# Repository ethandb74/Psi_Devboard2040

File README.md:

# Psi_Devboard2040

A custom built Devboard based of Rasberry-Pi RPI2040 microcontroller. Built with a focus on effeciency and simplicity. Provides as solid tool for future embedded systms project in C/C++ or Python. Very valuble learning experience. The most complex PCB project to date. This project was done as part of a larger electronics and robotics competition #Stasis. 

**This project is named after the greek letter Psi**

ART inspiration: I was inspired by the Greek Mythology, more specificlaly the greek god Poseidon and it formed the theme of this board :)

**Schematic**

Used Rasberry Board as reference

Implemnted new strategies and learned a lot doing this project

**PCB**

Complicated wiring for me. Took a while to puzzle out how to make all connections and get rid of DRC errors but very rewarding process. 

Learned during the PCB desin and routing the most. 

Final

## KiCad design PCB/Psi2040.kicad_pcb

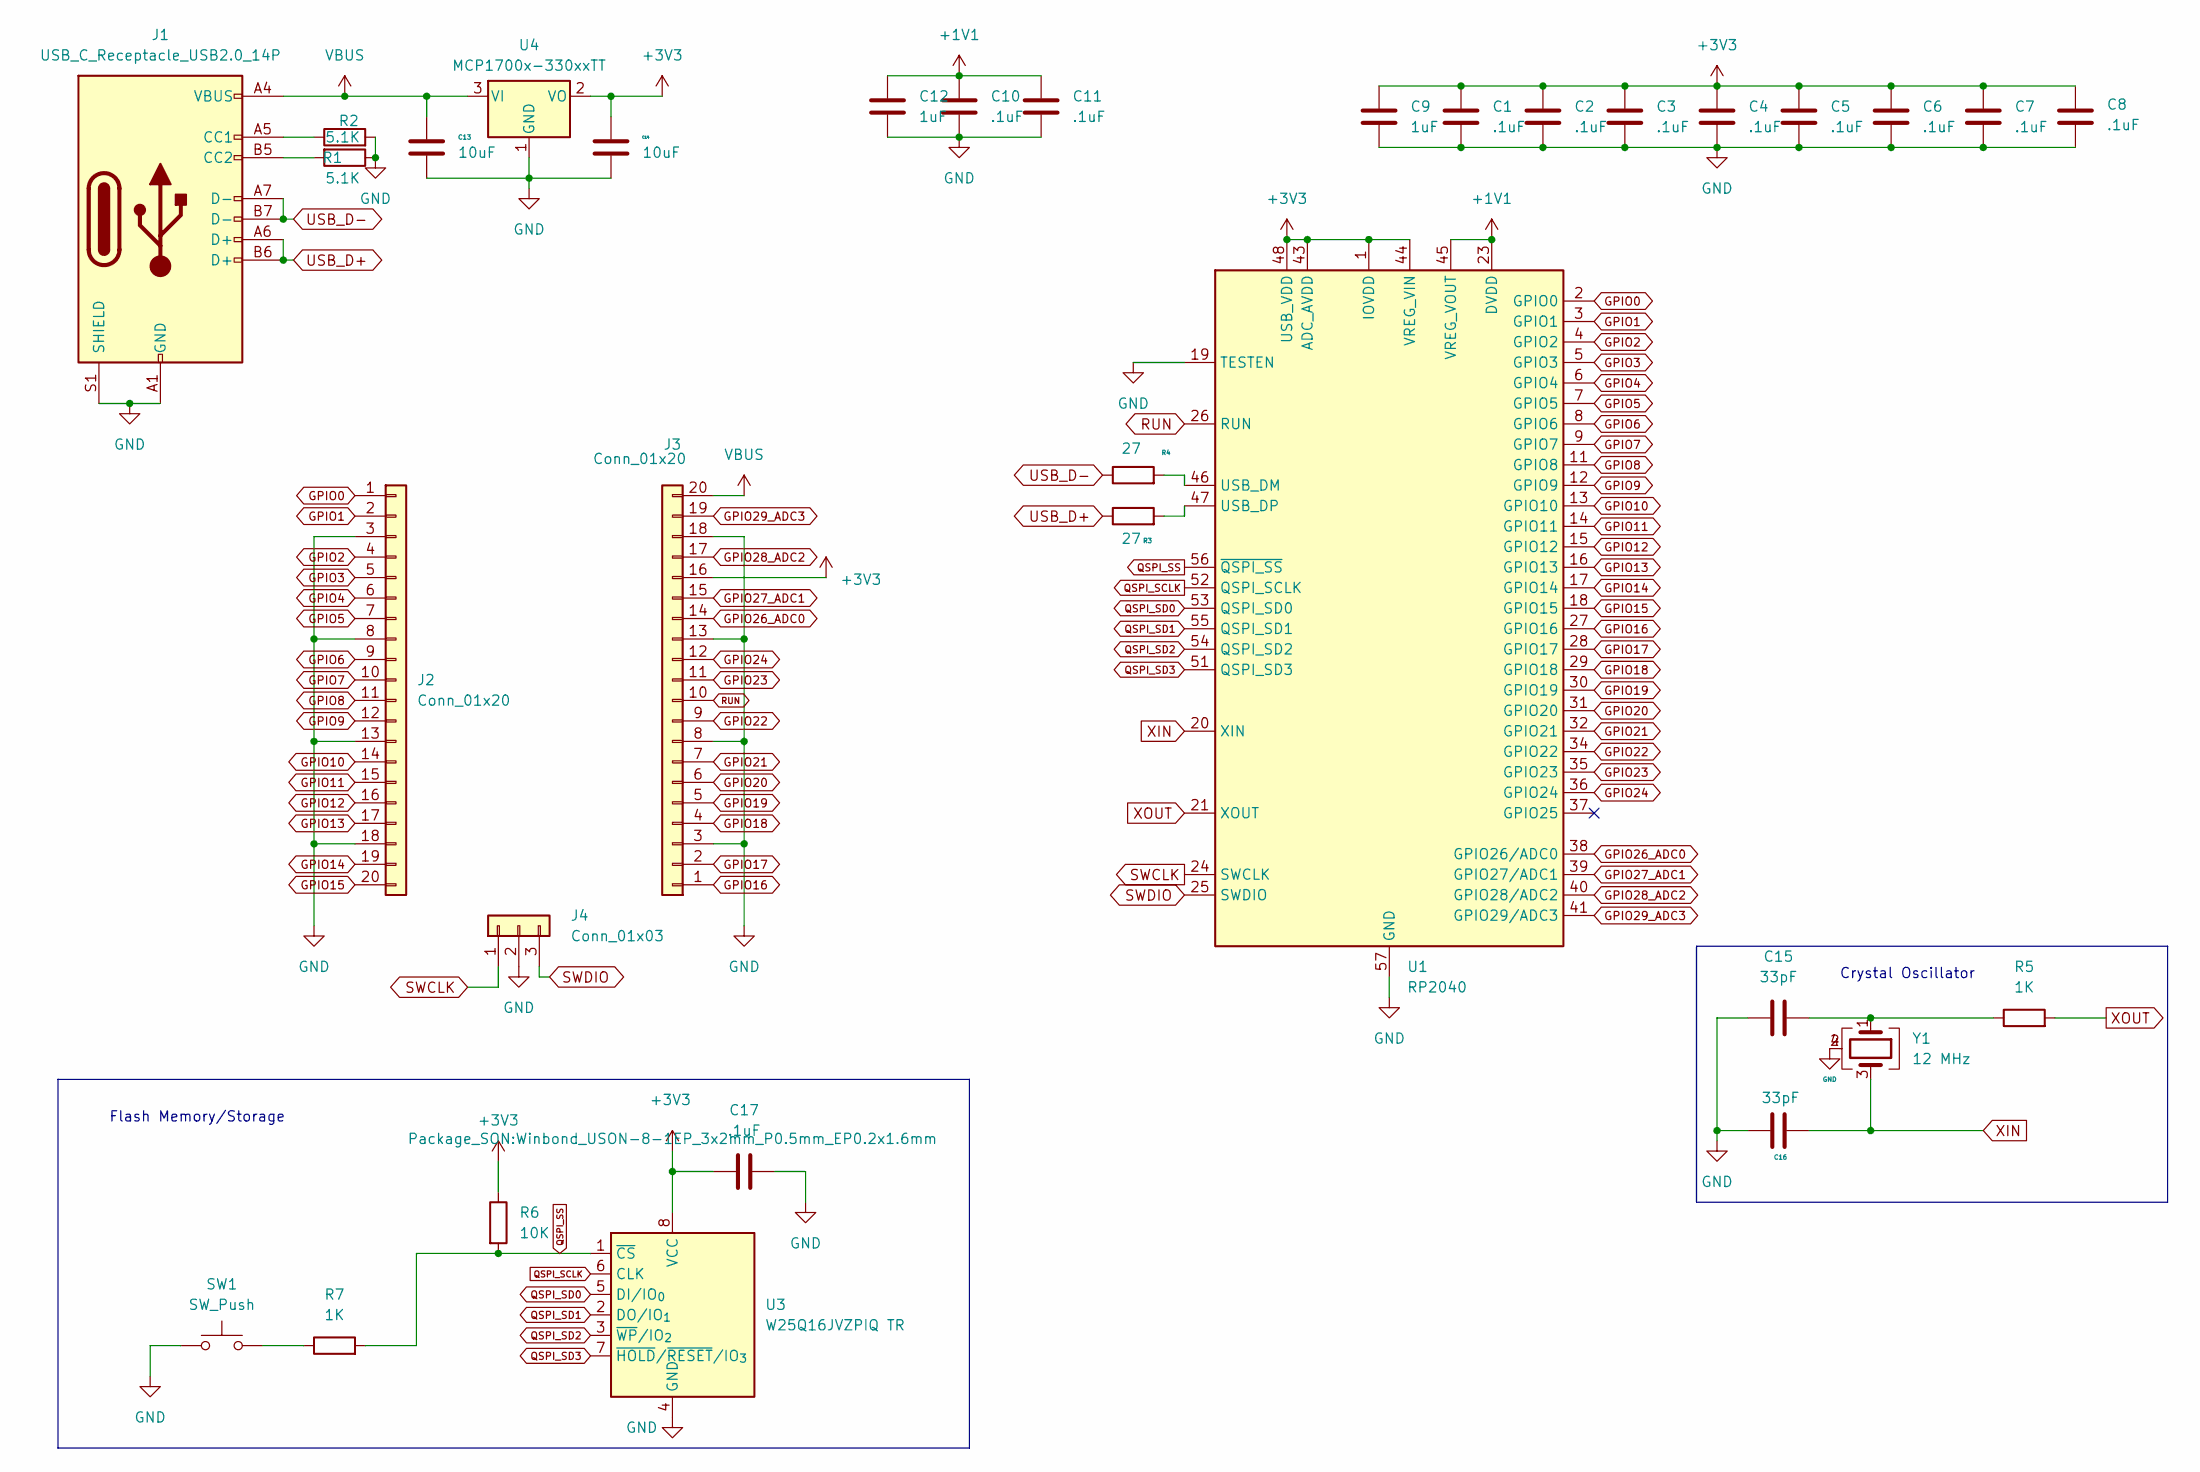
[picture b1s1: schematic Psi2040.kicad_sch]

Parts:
C1, C2, C3, C4, C5, C6, C7, C8, C10, C11, C17: .1uF; C_0402_1005Metric
C9, C12: 1uF; C_0402_1005Metric
C13, C14: 10uF; C_0402_1005Metric
C15, C16: 33pF; C_0402_1005Metric
J1: USB_C_Receptacle_USB2.0_14P; USB_C_Receptacle_HRO_TYPE-C-31-M-12
J2, J3: Conn_01x20; PinHeader_1x20_P2.54mm_Vertical
J4: Conn_01x03; PinHeader_1x03_P2.54mm_Vertical
R1, R2: 5.1K; R_0402_1005Metric
R3, R4: 27; R_0402_1005Metric
R5, R7: 1K; R_0402_1005Metric
R6: 10K; R_0402_1005Metric
SW1: SW_Push; SW_Push_SPST_NO_Alps_SKRK
U1: RP2040; QFN-56-1EP_7x7mm_P0.4mm_EP3.2x3.2mm
U3: W25Q16JVZPIQ TR; Winbond_USON-8-1EP_3x2mm_P0.5mm_EP0.2x1.6mm
U4: MCP1700x-330xxTT; SOT-23
Y1: 12 MHz; Crystal_SMD_3225-4Pin_3.2x2.5mm

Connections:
+1V1: C10.1, C11.1, C12.1, U1.23 (DVDD), U1.45 (VREG_VOUT), U1.50 (DVDD)
+3V3: C1.1, C2.1, C3.1, C4.1, C5.1, C6.1, C7.1, C8.1, C9.1, C14.1, C17.1, J3.16, R6.1, U1.1 (IOVDD), U1.10 (IOVDD), U1.22 (IOVDD), U1.33 (IOVDD), U1.42 (IOVDD), U1.43 (ADC_AVDD), U1.44 (VREG_VIN), U1.48 (USB_VDD), U1.49 (IOVDD), U3.8 (VCC), U4.2 (VO)
GND: C1.2, C2.2, C3.2, C4.2, C5.2, C6.2, C7.2, C8.2, C9.2, C10.2, C11.2, C12.2, C13.2, C14.2, C15.1, C16.1, C17.2, J1.A1 (GND), J1.A12 (GND), J1.B1 (GND), J1.B12 (GND), J1.S1 (SHIELD), J2.3, J2.8, J2.13, J2.18, J3.3, J3.8, J3.13, J3.18, J4.2, R1.1, R2.2, SW1.1, U1.19 (TESTEN), U1.57 (GND), U3.4 (GND), U4.1 (GND), Y1.2 (G), Y1.4 (G)
GPIO0: J2.1, U1.2 (GPIO0)
GPIO1: J2.2, U1.3 (GPIO1)
GPIO2: J2.4, U1.4 (GPIO2)
GPIO3: J2.5, U1.5 (GPIO3)
GPIO4: J2.6, U1.6 (GPIO4)
GPIO5: J2.7, U1.7 (GPIO5)
GPIO6: J2.9, U1.8 (GPIO6)
GPIO7: J2.10, U1.9 (GPIO7)
GPIO8: J2.11, U1.11 (GPIO8)
GPIO9: J2.12, U1.12 (GPIO9)
GPIO10: J2.14, U1.13 (GPIO10)
GPIO11: J2.15, U1.14 (GPIO11)
GPIO12: J2.16, U1.15 (GPIO12)
GPIO13: J2.17, U1.16 (GPIO13)
GPIO14: J2.19, U1.17 (GPIO14)
GPIO15: J2.20, U1.18 (GPIO15)
GPIO16: J3.1, U1.27 (GPIO16)
GPIO17: J3.2, U1.28 (GPIO17)
GPIO18: J3.4, U1.29 (GPIO18)
GPIO19: J3.5, U1.30 (GPIO19)
GPIO20: J3.6, U1.31 (GPIO20)
GPIO21: J3.7, U1.32 (GPIO21)
GPIO22: J3.9, U1.34 (GPIO22)
GPIO23: J3.11, U1.35 (GPIO23)
GPIO24: J3.12, U1.36 (GPIO24)
GPIO26_ADC0: J3.14, U1.38 (GPIO26/ADC0)
GPIO27_ADC1: J3.15, U1.39 (GPIO27/ADC1)
GPIO28_ADC2: J3.17, U1.40 (GPIO28/ADC2)
GPIO29_ADC3: J3.19, U1.41 (GPIO29/ADC3)
unnamed 32: C15.2, R5.1, Y1.1; also elsewhere on the board
unnamed: J1.A5 (CC1), R2.1
unnamed: J1.B5 (CC2), R1.2
unnamed: R7.1, SW1.2
unnamed: R4.2, U1.46 (USB_DM)
unnamed: R3.2, U1.47 (USB_DP)
QSPI_SCLK: U1.52 (QSPI_SCLK), U3.6 (CLK)
QSPI_SD0: U1.53 (QSPI_SD0), U3.5 (DI/IO_{0})
QSPI_SD1: U1.55 (QSPI_SD1), U3.2 (DO/IO_{1})
QSPI_SD2: U1.54 (QSPI_SD2), U3.3 (~WP/IO_{2})
QSPI_SD3: U1.51 (QSPI_SD3), U3.7 (~HOLD/~RESET/IO_{3})
QSPI_SS: R6.2, R7.2, U1.56 (~QSPI_SS), U3.1 (~CS)
RUN: J3.10, U1.26 (RUN)
SWCLK: J4.1, U1.24 (SWCLK)
SWDIO: J4.3, U1.25 (SWDIO)
USB_D+: J1.A6 (D+), J1.B6 (D+), R3.1
USB_D-: J1.A7 (D-), J1.B7 (D-), R4.1
VBUS: C13.1, J1.A4 (VBUS), J1.A9 (VBUS), J1.B4 (VBUS), J1.B9 (VBUS), J3.20, U4.3 (VI)
XIN: C16.2, U1.20 (XIN), Y1.3
XOUT: R5.2, U1.21 (XOUT); also elsewhere on the board

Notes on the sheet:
Flash Memory/Storage
Crystal Oscillator

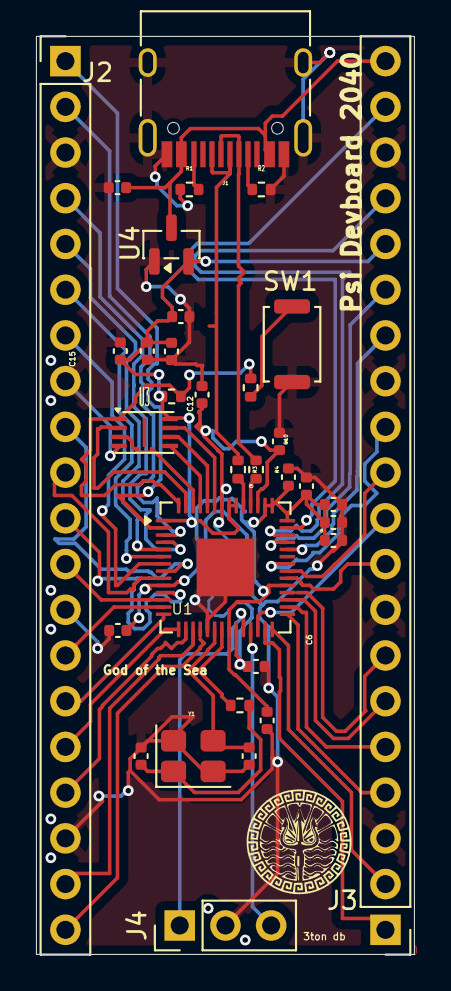
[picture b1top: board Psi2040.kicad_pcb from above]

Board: 2 copper layers, 21.0 x 51.0 mm, 34 parts (0 on the bottom side), 52 nets.

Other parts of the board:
3ton db: 1K; R_0402_1005Metric
Psi Devboard 2040: God of the Sea; psiimage

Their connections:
unnamed 32: 3ton db.1; also elsewhere on the board
XOUT: 3ton db.2; also elsewhere on the board

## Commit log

2026-04-14 Rename Psi2040.kicad_pcb to PCB/Psi2040.kicad_pcb
2026-04-14 Rename Psi2040.kicad_sch to PCB/Psi2040.kicad_sch
2026-04-14 Rename Psi2040.kicad_pro to PCB/Psi2040.kicad_pro
    overkill? Nah
2026-04-14 Rename Psi_Gerbers.zip to assets/Psi_Gerbers.zip
